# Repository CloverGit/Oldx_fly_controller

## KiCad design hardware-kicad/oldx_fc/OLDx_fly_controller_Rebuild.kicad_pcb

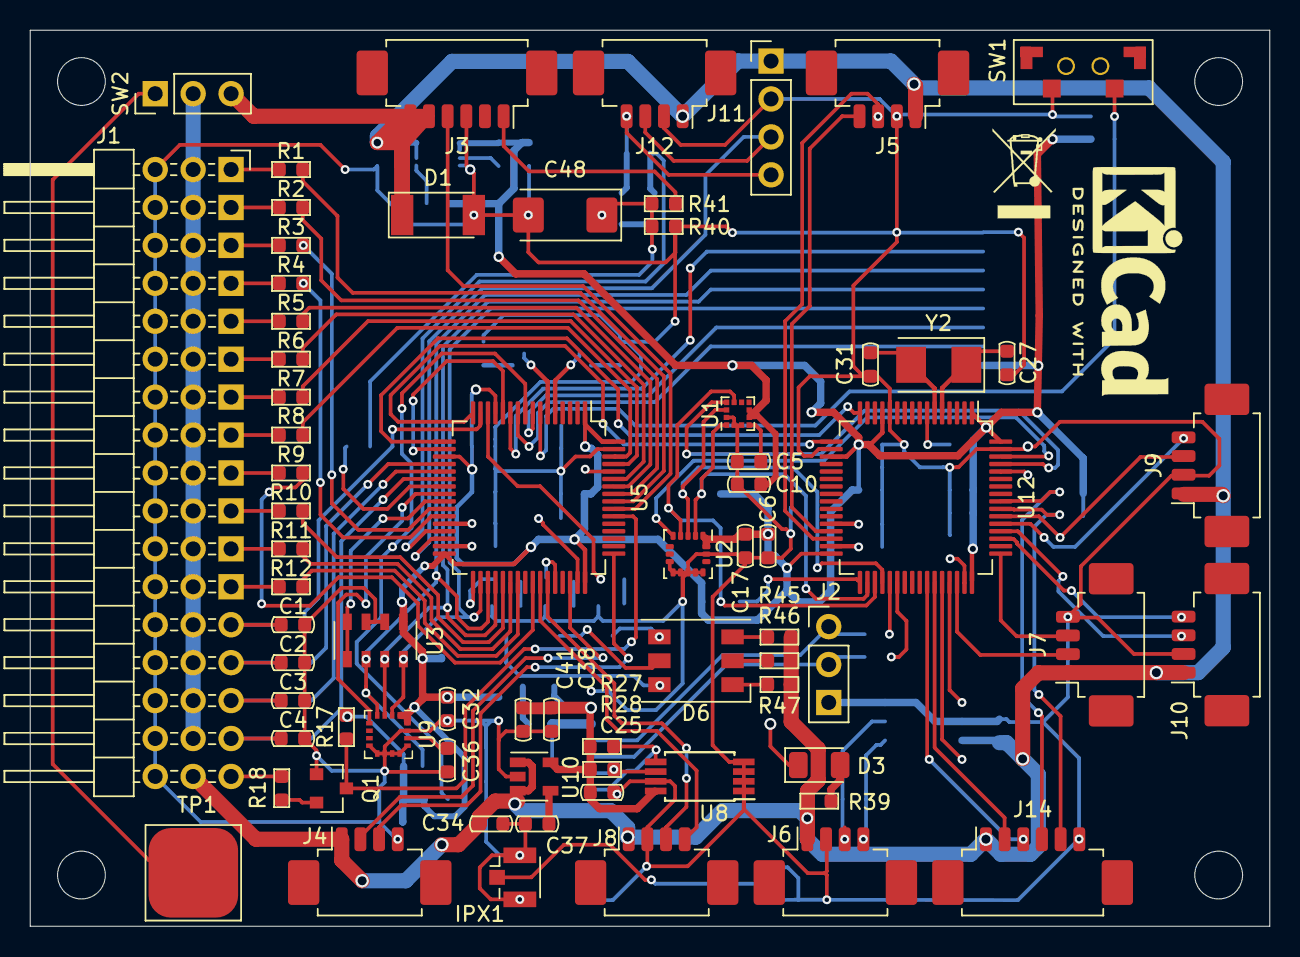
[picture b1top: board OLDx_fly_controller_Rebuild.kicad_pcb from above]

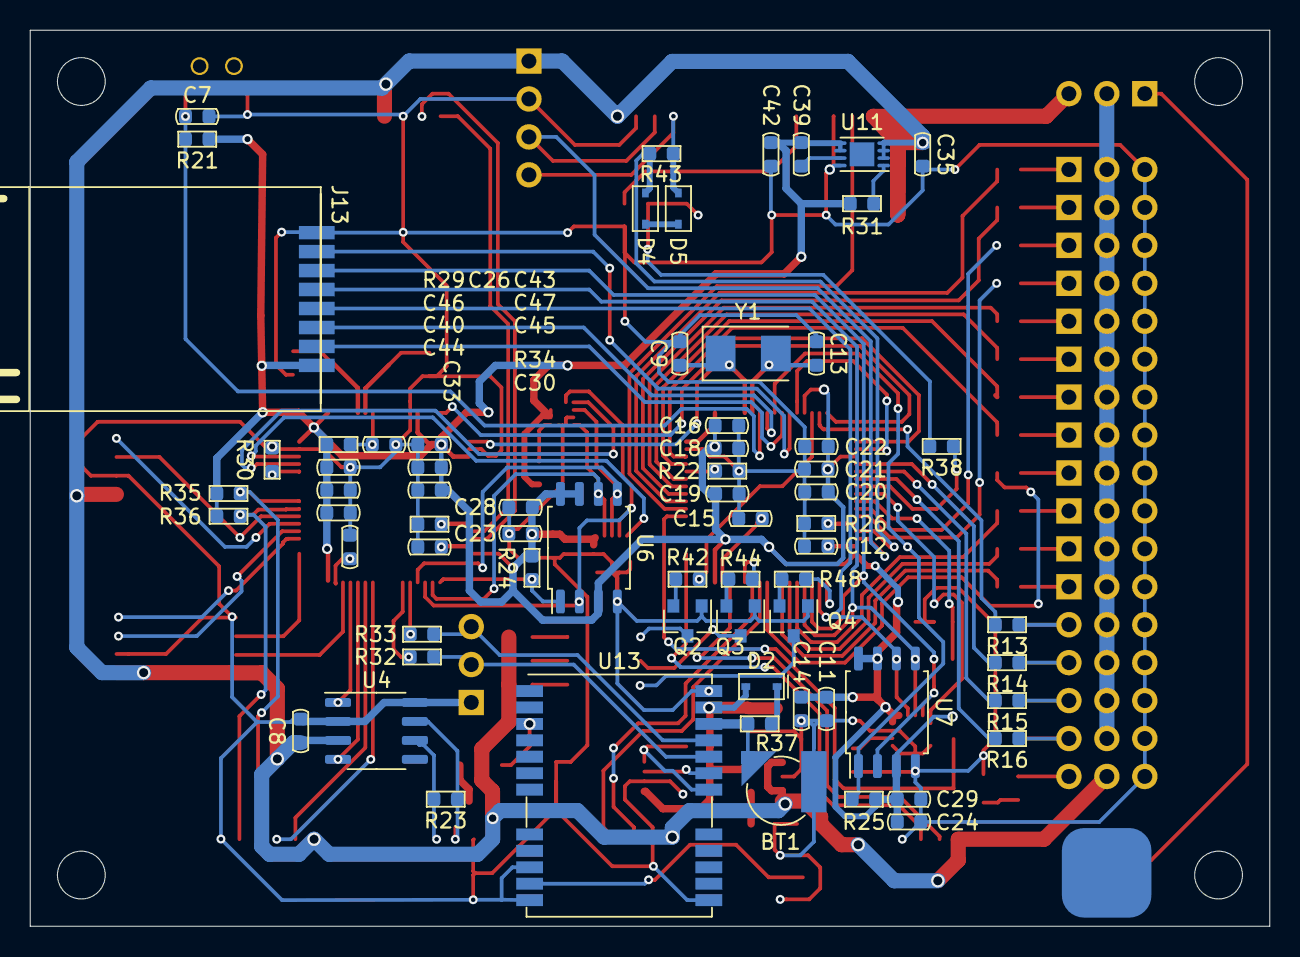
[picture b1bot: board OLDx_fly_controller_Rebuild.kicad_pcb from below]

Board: 2 copper layers, 83.0 x 60.0 mm, 144 parts (68 on the bottom side), 129 nets.

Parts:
BT1: XH414; XH414HG-IV01E
C1, C2, C3, C4, C28, C29, C34, C41: 1uF; C_0603_1608Metric2
C5: 100nF; C_0603_1608Metric2
C6, C8, C10, C14, C16, C17, C18, C19, C20, C21, C22, C23, C24, C25, C32, C36, C38, C40, C43, C44, C45, C46, C47: 0.1uF; C_0603_1608Metric2
C7, C39: 10nF; C_0603_1608Metric2
C9, C13: 20pF; C_0603_1608Metric2
C11, C35, C42: 4.7uF; C_0603_1608Metric2
C12, C15: 2.2uF; C_0603_1608Metric2
C26: 10NF; C_0603_1608Metric2
C27, C31: 20PF; C_0603_1608Metric2
C30, C33: 2.2UF; C_0603_1608Metric2
C37: 22nF; C_0603_1608Metric2
C48: 100uF; CP_EIA-6032-28_Kemet-C
D1: 1N47xxA; D_MELF
D2, D4, D5: BAT54WS; D_SOD-323-2
D3: LED; LED_1206_3216Metric
D6: 5050RGB; LED_WS2812_PLCC6_5.0x5.0mm_P1.6mm
H1, H2, H3, H4: M3; MountingHole_3.2mm_M3
IPX1: IPEX; U.FL_Hirose_U.FL-R-SMT-1_Vertical
J1: Conn_17X03; PinHeader_2x17_P2.54mm_Horizontal_copy
J2: PGPS; PinHeader_1x03_P2.54mm_Vertical
J3: POWER1; O_Molex_PicoBlade_53261-0671_1x06-1MP_P1.25mm_Horizontal
J4: SWD2; O_Molex_PicoBlade_53261-0471_1x04-1MP_P1.25mm_Horizontal
J5: SONAR1; O_Molex_PicoBlade_53261-0471_1x04-1MP_P1.25mm_Horizontal
J6: CAN1; O_Molex_PicoBlade_53261-0471_1x04-1MP_P1.25mm_Horizontal
J7: SWD1; O_Molex_PicoBlade_53261-0471_1x04-1MP_P1.25mm_Horizontal
J8: BLE1; O_Molex_PicoBlade_53261-0471_1x04-1MP_P1.25mm_Horizontal
J9: FLOW1; O_Molex_PicoBlade_53261-0471_1x04-1MP_P1.25mm_Horizontal
J10: IMU_BACK1; O_Molex_PicoBlade_53261-0471_1x04-1MP_P1.25mm_Horizontal
J11: PI1; PinHeader_1x04_P2.54mm_Vertical
J12: PI2; O_Molex_PicoBlade_53261-0471_1x04-1MP_P1.25mm_Horizontal
J13: NRF1; nRF24L01_PA&LNA
J14: GPS1; O_Molex_PicoBlade_53261-0671_1x06-1MP_P1.25mm_Horizontal
LOGO1: Logo_Open_Hardware_Small; KiCad-Logo2_6mm_SilkScreen
LOGO2: Logo_Open_Hardware_Small; WEEE-Logo_4.2x6mm_SilkScreen
Q1, Q2, Q3, Q4: S8050; SOT-23
R1, R2, R3, R4, R5, R6, R7, R8, R9, R10, R11, R12, R18, R38, R40, R42, R44, R48: 1K; R_0603_1608Metric2
R13, R14, R15, R16, R45, R46, R47: 100R; R_0603_1608Metric2
R17, R21, R22, R24, R25, R26, R29, R30, R34, R41: 10K; R_0603_1608Metric2
R23, R32, R33, R37: 120R; R_0603_1608Metric2
R27, R28, R35, R36: 4.7K; R_0603_1608Metric2
R31: 100K; R_0603_1608Metric2
R39: 510R; R_0603_1608Metric2
R43: NC; R_0603_1608Metric2
SW1: RST_FC; Switch_3X6X3.5
SW2: SW_SPDT; PinHeader_1x03_P2.54mm_Vertical
TP1: 5V_OUT; TestPoint_Pad_6.0x6.0mm
U1: LIS3MDL; LGA-12_2x2mm_P0.5mm
U2: LSM6DS33; LGA-16_3x3mm_P0.5mm_LayoutBorder3x5y
U3: MS5611; MS5611-01BA03
U4: TJA1050; SO-8_3.9x4.9mm_P1.27mm
U5, U12: STM32F405RGTx; LQFP-64_10x10mm_P0.5mm
U6, U7: W25X16; SOIC-8_5.275x5.275mm_P1.27mm
U8: 24C32; TSSOP-8_4.4x3mm_P0.65mm
U9: ICM20602; LGA-16_3x3mm_P0.5mm
U10: RT9193-33; SOT-23-5
U11: AS1364-BTDT-33; TDFN-8-1EP_3x2mm_P0.5mm_EP1.80x1.65mm
U13: GPS_NEO-8; ublox_NEO
Y1, Y2: 8MHZ; Crystal_SMD_5032-2Pin_5.0x3.2mm

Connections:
+3V3: C6.2, C10.1, C11.2, C14.2, C16.2, C17.2, C18.2, C19.2, C20.2, C21.2, C22.2, C23.1, C24.1, C28.1, C29.1, C32.2, C39.2, C40.2, C42.2, C43.2, C44.2, C45.2, C46.2, C47.2, J13.1, R17.2, R21.1, R24.2, R25.2, R29.1, R31.1, R35.1, R36.1, U1.5, U1.6, U2.1, U2.16, U3.1, U5.1, U5.13, U5.19, U5.32, U5.48, U5.64, U6.3, U6.7, U6.8, U7.3, U7.7, U7.8, U9.1, U9.16, U11.5, U11.6, U12.1, U12.13, U12.19, U12.32, U12.48, U12.64
+5V: C8.2, C34.1, C35.2, D1.1, J1.Q2, J3.1, J3.2, J4.4, J5.4, J6.4, J7.4, J8.4, J9.4, J10.4, J11.1, J12.4, J14.6, R39.1, R45.1, R46.1, R47.1, SW2.3, U4.3, U10.1, U10.3, U11.2, U11.3, U11.4
/3.3VG: C25.1, C38.1, C41.1, D2.1, R27.2, R28.2, U8.8, U10.5, U13.23
/BAT: R38.1, U5.23
/BEEP: J3.3, U5.55
/CANH: J6.2, R23.1, U4.7
/CANL: J6.1, R23.2, U4.6
/CANRX: U4.4, U12.44
/CANTX: U4.1, U12.45
/CS1: U5.24, U9.5
/CS1_IMU: U1.10, U12.61
/CS2: U3.4, U3.5, U5.25
/CS2_IMU: U2.5, U12.62
/CS3: J13.3, U5.8
/CS4: R25.1, U5.9, U7.1
/FLASH_CS: R24.1, U6.1, U12.33
/GROUND1: R13.2, U5.15
/GROUND2: R14.2, U5.20
/GROUND3: R15.2, U5.21
/GROUND4: R16.2, U5.22
/IIC_SCLG: R28.1, U8.6, U13.19
/IIC_SDAG: R27.1, U8.5, U13.18
/LED_11: R42.1, U5.14
/LED_12: R44.1, U5.44
/LED_13: R48.1, U5.33
/NRF_CE: J13.2, U5.10
/NRF_IRQ: J13.7, U5.11
/PWM1: R1.1, U5.56
/PWM2: R2.1, U5.57
/PWM3: R3.1, U5.26
/PWM4: R4.1, U5.27
/PWM5: R5.1, U5.58
/PWM6: R6.1, U5.59
/PWM7: R7.1, U5.61
/PWM8: R8.2, U5.62
/PWM9: R9.1, U5.41
/PWM10: R10.1, U5.37
/PWM11: R11.1, U5.38
/PWM12: R12.1, U5.39
/P_LEG: J1.A2, J1.B2, J1.C2, J1.D2, J1.E2, J1.F2, J1.G2, J1.H2, J1.I2, J1.J2, J1.K2, J1.L2, J1.M2, J1.N2, J1.O2, J1.P2, SW2.2
/RST_FC: C7.1, R21.2, SW1.2, U5.7
/SCLK_FC: J4.2, U5.49
/SCLK_IMU: J7.2, U12.49
/SCL_B: J14.3, R35.2, U12.56
/SDA_B: J14.2, R36.2, U12.55
/SPI3_CK: J13.4, U3.8, U5.34, U7.6, U9.2
/SPI3_CK_IMU: U1.1, U2.2, U6.6, U12.34
/SPI3_SI: J13.5, U3.7, U5.36, U7.5, U9.3
/SPI3_SI_IMU: U1.11, U2.3, U6.5, U12.36
/SPI3_SO: J13.6, U3.6, U5.35, U7.2, U9.4
/SPI3_SO_IMU: U1.9, U2.4, U6.2, U12.35
/SWD_FC: J4.3, U5.46
/SWD_IMU: J7.3, U12.46
/UART1_R_1: J8.2, U5.43
/UART1_R_2: J14.5, U12.43
/UART1_T_1: J8.1, U5.42
/UART1_T_2: J14.4, U12.42
/UART2_R_1: U5.17, U12.16
/UART2_R_2: U5.16, U12.17
/UART3_R_1: J11.3, J12.2, U5.30
/UART3_R_2: J5.2, U12.30
/UART3_T_1: D4.1, R43.2, U5.29
/UART3_T_2: J5.1, U12.29
/UART4_R_2: J10.2, U12.52
/UART4_T_2: J10.1, U12.51
/UART5_R_1: Q1.3, R17.1, U5.54
/UART5_R_2: J9.2, U12.54
/UART5_T_2: J9.1, U12.53
/UART6_R_2: R32.2, U12.38
/UART6_T_2: R33.2, U12.37
GND: BT1.2, C1.2, C2.2, C3.2, C4.2, C5.2, C6.1, C7.2, C8.1, C9.2, C10.2, C11.1, C12.2, C13.2, C14.1, C15.2, C16.1, C17.1, C18.1, C19.1, C20.1, C21.1, C22.1, C23.2, C24.2, C25.2, C26.2, C27.2, C28.2, C29.2, C30.2, C31.2, C32.1, C33.2, C34.2, C35.1, C36.1, C37.2, C38.2, C40.1, C41.2, C42.1, C43.1, C44.1, C45.1, C46.1, C47.1, C48.2, D1.2, IPX1.2, J1.A3, J1.B3, J1.C3, J1.D3, J1.E3, J1.F3, J1.G3, J1.H3, J1.I3, J1.J3, J1.K3, J1.L3, J1.M1, J1.N1, J1.O1, J1.P1, J1.Q1, J2.3, J3.4, J4.1, J5.3, J6.3, J7.1, J8.3, J9.3, J10.3, J11.2, J12.3, J13.8, J14.1, Q1.1, Q2.1, Q3.1, Q4.1, R22.2, R26.1, R30.2, R34.1, R40.2, SW1.1, U1.2, U1.3, U1.12, U2.8, U2.9, U2.10, U2.11, U2.12, U2.13, U2.15, U3.2, U3.3, U4.2, U4.8, U5.63, U6.4, U7.4, U8.1, U8.2, U8.3, U8.4, U8.7, U9.8, U9.9, U9.10, U9.11, U9.12, U9.13, U9.15, U10.2, U11.8, U12.12, U12.18, U12.63, U13.10, U13.12, U13.13, U13.24
unnamed: BT1.1, R37.2, U13.22
unnamed: C1.1, J1.M3, R13.1
unnamed: C2.1, J1.N3, R14.1
unnamed: C3.1, J1.O3, R15.1
unnamed: C4.1, J1.P3, R16.1
unnamed: C5.1, U1.4
unnamed: C9.1, U5.5, Y1.1
unnamed: C12.1, U5.31
unnamed: C13.1, U5.6, Y1.2
unnamed: C15.1, U5.47
unnamed: C26.1, R29.2, U12.7
unnamed: C27.1, U12.5, Y2.1
unnamed: C30.1, U12.31
unnamed: C31.1, U12.6, Y2.2
unnamed: C33.1, U12.47
unnamed: C36.2, U9.14
unnamed: C37.1, U10.4
unnamed: C39.1, U11.7
unnamed: C48.1, R38.2, R40.1, R41.1
unnamed: D2.2, R37.1
unnamed: D3.1, U13.3
unnamed: D3.2, R39.2
unnamed: D4.2, D5.1
unnamed: D5.2, J11.4, J12.1, R43.1
unnamed: D6.1, R47.2
unnamed: D6.2, R46.2
unnamed: D6.3, R45.2
unnamed: D6.4, Q2.3
unnamed: D6.5, Q3.3
unnamed: D6.6, Q4.3
unnamed: IPX1.1, U13.11
unnamed: J1.A1, R1.2
unnamed: J1.B1, R2.2
unnamed: J1.C1, R3.2
unnamed: J1.D1, R4.2
unnamed: J1.E1, R5.2
unnamed: J1.F1, R6.2
unnamed: J1.G1, R7.2
unnamed: J1.H1, R8.1
unnamed: J1.I1, R9.2
unnamed: J1.J1, R10.2
unnamed: J1.K1, R11.2
unnamed: J1.L1, R12.2
unnamed: J1.Q3, R18.1
unnamed: J2.1, R33.1, U13.21
unnamed: J2.2, R32.1, U13.20
unnamed: J3.6, R41.2
unnamed: Q1.2, R18.2
unnamed: Q2.2, R42.2
unnamed: Q3.2, R44.2
unnamed: Q4.2, R48.2
unnamed: R22.1, U5.60
unnamed: R26.2, U5.28
unnamed: R30.1, U12.60
unnamed: R31.2, U11.1
unnamed: R34.2, U12.28
unnamed: SW2.1, TP1.1
unnamed: U5.12, U5.18

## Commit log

2020-03-14 Create LICENSE
2020-03-14 schematic rerew by CloverGit
2020-03-15 Fix a bug
2020-03-15 Add library
2020-03-15 update ignore files
2020-04-30 Update PCB file
2020-04-30 Update files
